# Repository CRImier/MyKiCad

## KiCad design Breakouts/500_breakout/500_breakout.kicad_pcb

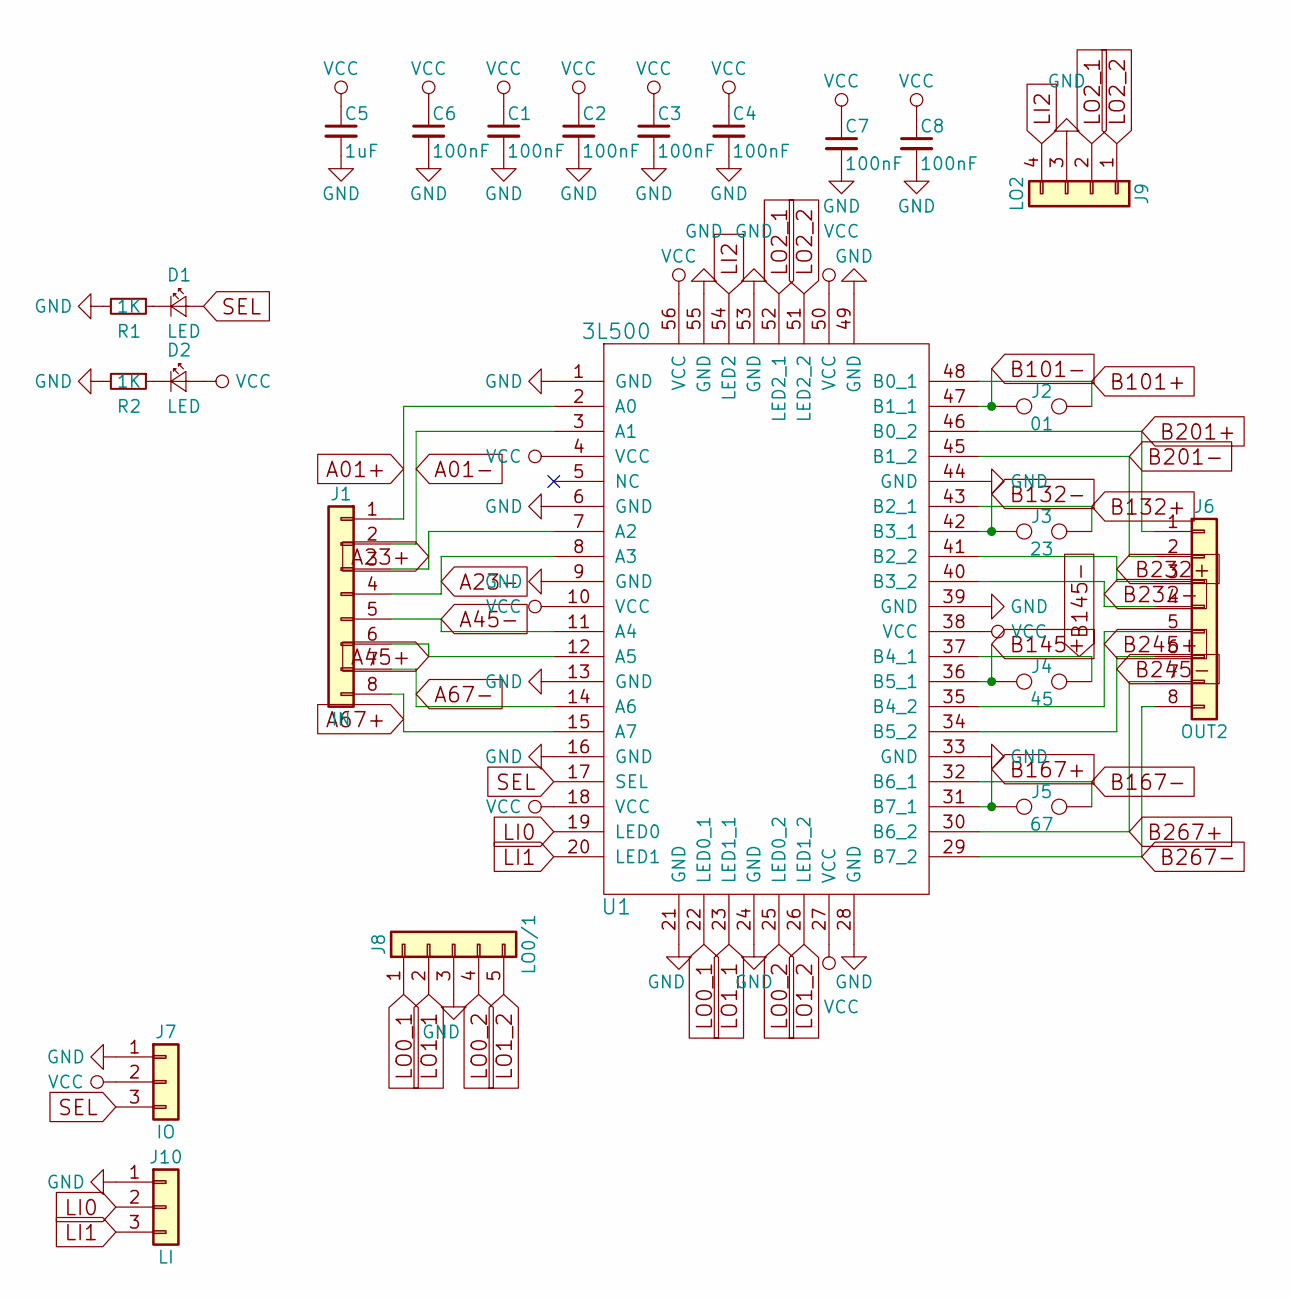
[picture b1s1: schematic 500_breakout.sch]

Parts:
C1, C2, C3, C4, C6, C7, C8: 100nF; C_0603
C5: 1uF; C_0603
D1, D2: LED; LED_0805
J1: IN; Pin_Header_Straight_1x08_Pitch2.00mm
J2: 01; Pin_Header_Straight_1x02_Pitch1.27mm
J3: 23; Pin_Header_Straight_1x02_Pitch1.27mm
J4: 45; Pin_Header_Straight_1x02_Pitch1.27mm
J5: 67; Pin_Header_Straight_1x02_Pitch1.27mm
J6: OUT2; Pin_Header_Straight_1x08_Pitch2.00mm
J7: IO; Pin_Header_Straight_1x03_Pitch2.54mm
J8: LO0/1; Pin_Header_Straight_1x05_Pitch2.00mm
J9: LO2; Pin_Header_Straight_1x04_Pitch2.00mm
J10: LI; Pin_Header_Straight_1x03_Pitch2.54mm
R1, R2: 1K; R_0805
U1: 3L500; R-PWQFN-N56

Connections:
A01+: J1.1, U1.2 (A0)
A01-: J1.2, U1.3 (A1)
A23+: J1.3, U1.7 (A2)
A23-: J1.4, U1.8 (A3)
A45+: J1.6, U1.12 (A5)
A45-: J1.5, U1.11 (A4)
A67+: J1.8, U1.15 (A7)
A67-: J1.7, U1.14 (A6)
B101+: J2.2, U1.48 (B0_1)
B101-: J2.1, U1.47 (B1_1)
B132+: J3.2, U1.43 (B2_1)
B132-: J3.1, U1.42 (B3_1)
B145+: J4.1, U1.36 (B5_1)
B145-: J4.2, U1.37 (B4_1)
B167+: J5.1, U1.31 (B7_1)
B167-: J5.2, U1.32 (B6_1)
B201+: J6.1, U1.46 (B0_2)
B201-: J6.2, U1.45 (B1_2)
B232+: J6.3, U1.41 (B2_2)
B232-: J6.4, U1.40 (B3_2)
B245+: J6.5, U1.35 (B4_2)
B245-: J6.6, U1.34 (B5_2)
B267+: J6.7, U1.30 (B6_2)
B267-: J6.8, U1.29 (B7_2)
GND: C1.2, C2.2, C3.2, C4.2, C5.2, C6.2, C7.2, C8.2, J7.1, J8.3, J9.3, J10.1, R1.2, R2.2, U1.1 (GND), U1.6 (GND), U1.9 (GND), U1.13 (GND), U1.16 (GND), U1.21 (GND), U1.24 (GND), U1.28 (GND), U1.33 (GND), U1.39 (GND), U1.44 (GND), U1.49 (GND), U1.53 (GND), U1.55 (GND)
LI0: J10.2, U1.19 (LED0)
LI1: J10.3, U1.20 (LED1)
LI2: J9.4, U1.54 (LED2)
LO0_1: J8.1, U1.22 (LED0_1)
LO0_2: J8.4, U1.25 (LED0_2)
LO1_1: J8.2, U1.23 (LED1_1)
LO1_2: J8.5, U1.26 (LED1_2)
LO2_1: J9.2, U1.52 (LED2_1)
LO2_2: J9.1, U1.51 (LED2_2)
unnamed: D1.1 (K), R1.1
unnamed: D2.1 (K), R2.1
SEL: D1.2 (A), J7.3, U1.17 (SEL)
VCC: C1.1, C2.1, C3.1, C4.1, C5.1, C6.1, C7.1, C8.1, D2.2 (A), J7.2, U1.4 (VCC), U1.10 (VCC), U1.18 (VCC), U1.27 (VCC), U1.38 (VCC), U1.50 (VCC), U1.56 (VCC)

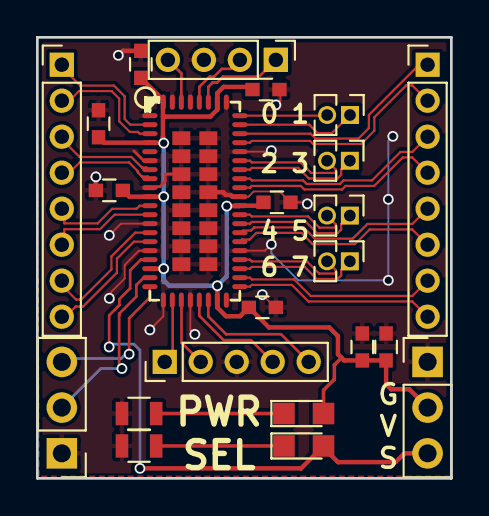
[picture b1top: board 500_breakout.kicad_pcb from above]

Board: 2 copper layers, 23.0 x 24.5 mm, 23 parts (0 on the bottom side), 38 nets.

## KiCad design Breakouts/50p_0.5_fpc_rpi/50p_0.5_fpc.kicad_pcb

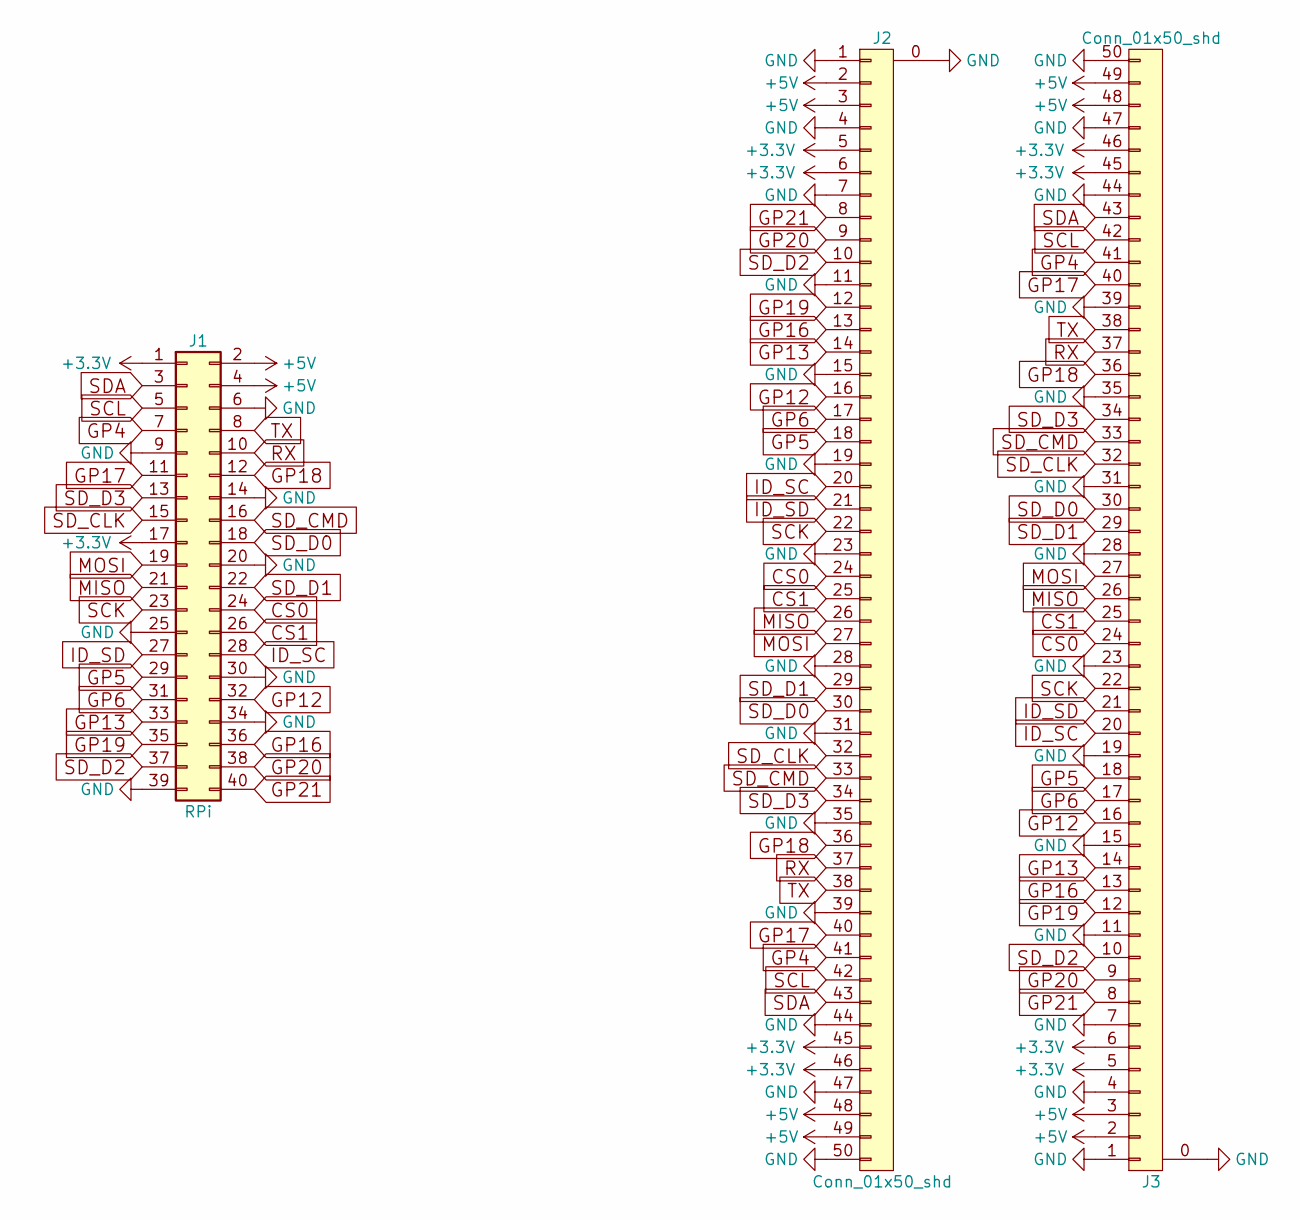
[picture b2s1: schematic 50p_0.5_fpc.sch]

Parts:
J1: RPi; Pin_Header_Straight_2x20_Pitch2.54mm
J2, J3: Conn_01x50_shd; FPC_50

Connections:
+3V3: J1.1, J1.17, J2.5, J2.6, J2.45, J2.46, J3.5, J3.6, J3.45, J3.46
+5V: J1.2, J1.4, J2.2, J2.3, J2.48, J2.49, J3.2, J3.3, J3.48, J3.49
CS0: J1.24, J2.24, J3.24
CS1: J1.26, J2.25, J3.25
GND: J1.6, J1.9, J1.14, J1.20, J1.25, J1.30, J1.34, J1.39, J2.0, J2.1, J2.4, J2.7, J2.11, J2.15, J2.19, J2.23, J2.28, J2.31, J2.35, J2.39, J2.44, J2.47, J2.50, J3.0, J3.1, J3.4, J3.7, J3.11, J3.15, J3.19, J3.23, J3.28, J3.31, J3.35, J3.39, J3.44, J3.47, J3.50
GP4: J1.7, J2.41, J3.41
GP5: J1.29, J2.18, J3.18
GP6: J1.31, J2.17, J3.17
GP12: J1.32, J2.16, J3.16
GP13: J1.33, J2.14, J3.14
GP16: J1.36, J2.13, J3.13
GP17: J1.11, J2.40, J3.40
GP18: J1.12, J2.36, J3.36
GP19: J1.35, J2.12, J3.12
GP20: J1.38, J2.9, J3.9
GP21: J1.40, J2.8, J3.8
ID_SC: J1.28, J2.20, J3.20
ID_SD: J1.27, J2.21, J3.21
MISO: J1.21, J2.26, J3.26
MOSI: J1.19, J2.27, J3.27
RX: J1.10, J2.37, J3.37
SCK: J1.23, J2.22, J3.22
SCL: J1.5, J2.42, J3.42
SDA: J1.3, J2.43, J3.43
SD_CLK: J1.15, J2.32, J3.32
SD_CMD: J1.16, J2.33, J3.33
SD_D0: J1.18, J2.30, J3.30
SD_D1: J1.22, J2.29, J3.29
SD_D2: J1.37, J2.10, J3.10
SD_D3: J1.13, J2.34, J3.34
TX: J1.8, J2.38, J3.38

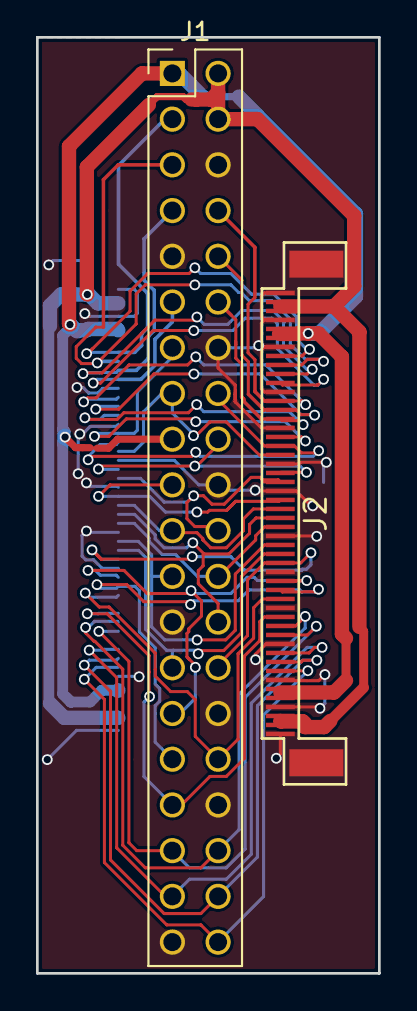
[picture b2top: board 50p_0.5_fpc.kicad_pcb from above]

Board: 2 copper layers, 19.0 x 52.0 mm, 3 parts (1 on the bottom side), 31 nets.

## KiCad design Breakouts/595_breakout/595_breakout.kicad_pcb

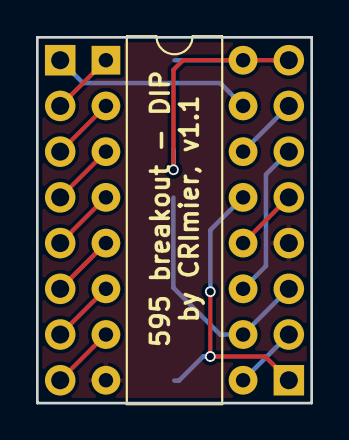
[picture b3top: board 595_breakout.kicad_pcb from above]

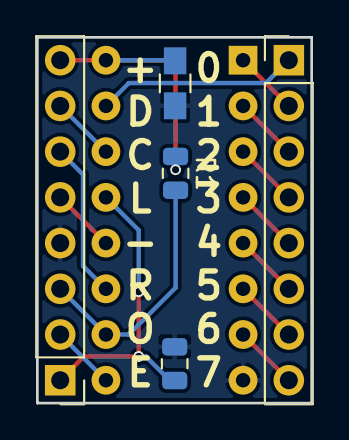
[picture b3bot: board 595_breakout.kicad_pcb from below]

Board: 2 copper layers, 15.2 x 20.3 mm, 6 parts (5 on the bottom side), 16 nets.

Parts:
C1: C_Small; C_0805_HandSoldering
J1, J2: Conn_01x08; Pin_Header_Straight_1x08_Pitch2.54mm
R1, R2: R_Small; R_0805_2012Metric
U1: 74LS595; DIP-16_W7.62mm

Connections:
CLK: J1.6, U1.11
DIN: J1.7, U1.14
DOUT: J1.2, U1.9
GND: C1.2, J1.4, R2.2, U1.8
LATCH: J1.5, U1.12
unnamed: J2.1, U1.15
unnamed: J2.2, U1.1
unnamed: J2.3, U1.2
unnamed: J2.4, U1.3
unnamed: J2.5, U1.4
unnamed: J2.6, U1.5
unnamed: J2.7, U1.6
unnamed: J2.8, U1.7
OE: J1.1, R2.1, U1.13
RST: J1.3, R1.2, U1.10
VCC: C1.1, J1.8, R1.1, U1.16

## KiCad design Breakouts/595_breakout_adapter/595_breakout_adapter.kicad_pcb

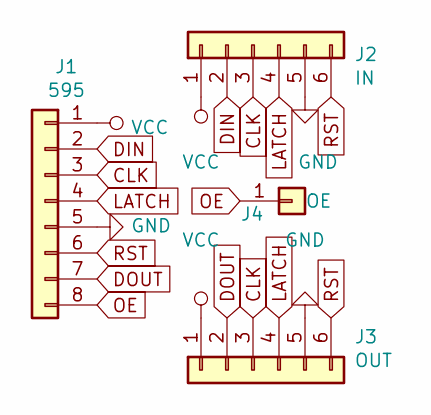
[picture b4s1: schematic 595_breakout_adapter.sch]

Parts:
J1: 595; PinHeader_1x08_P2.54mm_Vertical
J2: IN; PinHeader_1x06_P2.54mm_Vertical
J3: OUT; PinHeader_1x06_P2.54mm_Vertical
J4: OE; PinHeader_1x01_P2.54mm_Vertical

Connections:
CLK: J1.3, J2.3, J3.3
DIN: J1.2, J2.2
DOUT: J1.7, J3.2
GND: J1.5, J2.5, J3.5
LATCH: J1.4, J2.4, J3.4
OE: J1.8, J4.1
RST: J1.6, J2.6, J3.6
VCC: J1.1, J2.1, J3.1

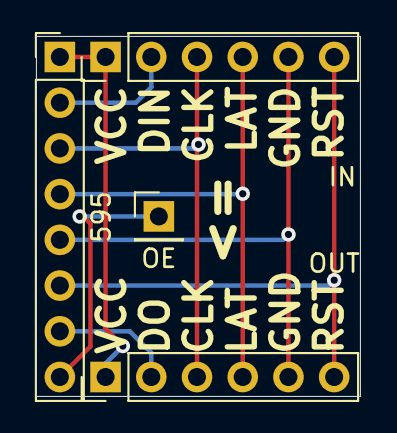
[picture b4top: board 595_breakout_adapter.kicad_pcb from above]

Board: 2 copper layers, 18.0 x 20.0 mm, 4 parts (0 on the bottom side), 8 nets.

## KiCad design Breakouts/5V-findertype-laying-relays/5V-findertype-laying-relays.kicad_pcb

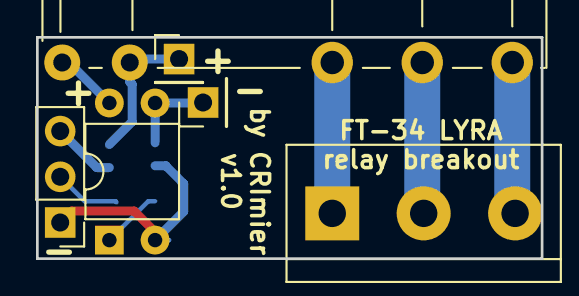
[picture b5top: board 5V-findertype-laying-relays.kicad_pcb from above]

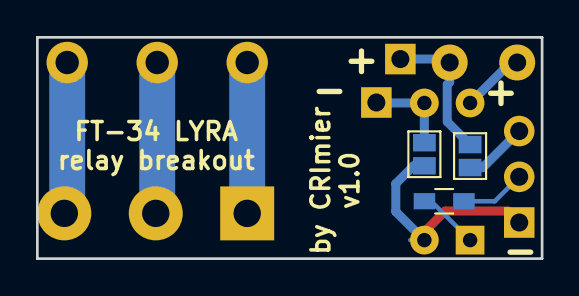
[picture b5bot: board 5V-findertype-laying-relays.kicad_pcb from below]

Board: 2 copper layers, 28.0 x 12.3 mm, 9 parts (3 on the bottom side), 10 nets.

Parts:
J1: Conn_01x03; Pin_Header_Straight_1x03_Pitch2.54mm
J2, J4: Conn_01x01; Pin_Header_Straight_1x01_Pitch2.54mm
J3: Conn_01x03; TerminalBlock_bornier-3_P5.08mm
JP1, JP2: Jumper; GS2
K1: FINDER-40.31; Relay_SPDT_SingleRow_Laying_FinderType34Point51
R1: 1k; R_0603_HandSoldering
U1: PC817; DIP-4_W7.62mm

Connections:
GND: J1.1, JP2.1, U1.2
unnamed: J4.1, JP1.2, K1.A1
unnamed: K1.A2, U1.4
unnamed: J1.2, R1.2
unnamed: J2.1, JP2.2, U1.3
unnamed: J3.1, K1.12
unnamed: J3.2, K1.11
unnamed: J3.3, K1.14
unnamed: R1.1, U1.1
VCC: J1.3, JP1.1

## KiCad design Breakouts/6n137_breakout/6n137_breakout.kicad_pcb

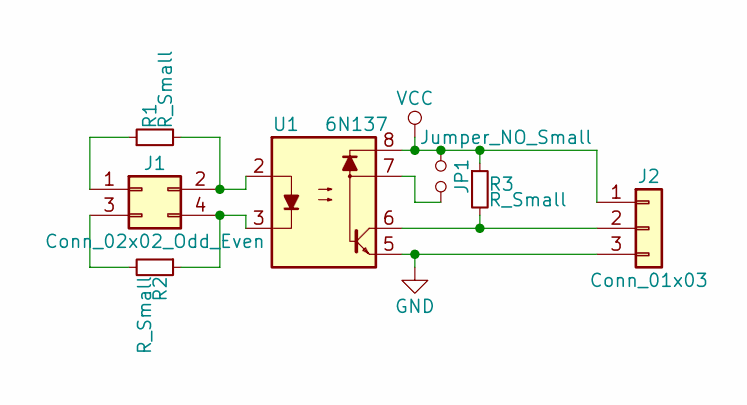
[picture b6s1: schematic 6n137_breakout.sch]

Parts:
J1: Conn_02x02_Odd_Even; Pin_Header_Straight_2x02_Pitch2.54mm
J2: Conn_01x03; Pin_Header_Straight_1x03_Pitch2.54mm
JP1: Jumper_NO_Small; GS2
R1, R2: R_Small; R_0603
R3: R_Small; R_0603_HandSoldering
U1: 6N137; DIP-8_W7.62mm

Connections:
GND: J2.3, U1.5
unnamed: J1.1, R1.1
unnamed: J1.2, R1.2, U1.2
unnamed: J1.3, R2.2
unnamed: J1.4, R2.1, U1.3
unnamed: J2.2, R3.2, U1.6
unnamed: JP1.2, U1.7
VCC: J2.1, JP1.1, R3.1, U1.8

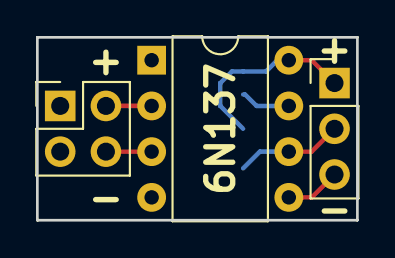
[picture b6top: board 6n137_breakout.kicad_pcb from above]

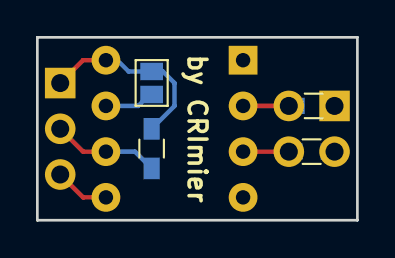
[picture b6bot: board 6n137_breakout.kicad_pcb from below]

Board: 2 copper layers, 17.8 x 10.2 mm, 7 parts (4 on the bottom side), 8 nets.
